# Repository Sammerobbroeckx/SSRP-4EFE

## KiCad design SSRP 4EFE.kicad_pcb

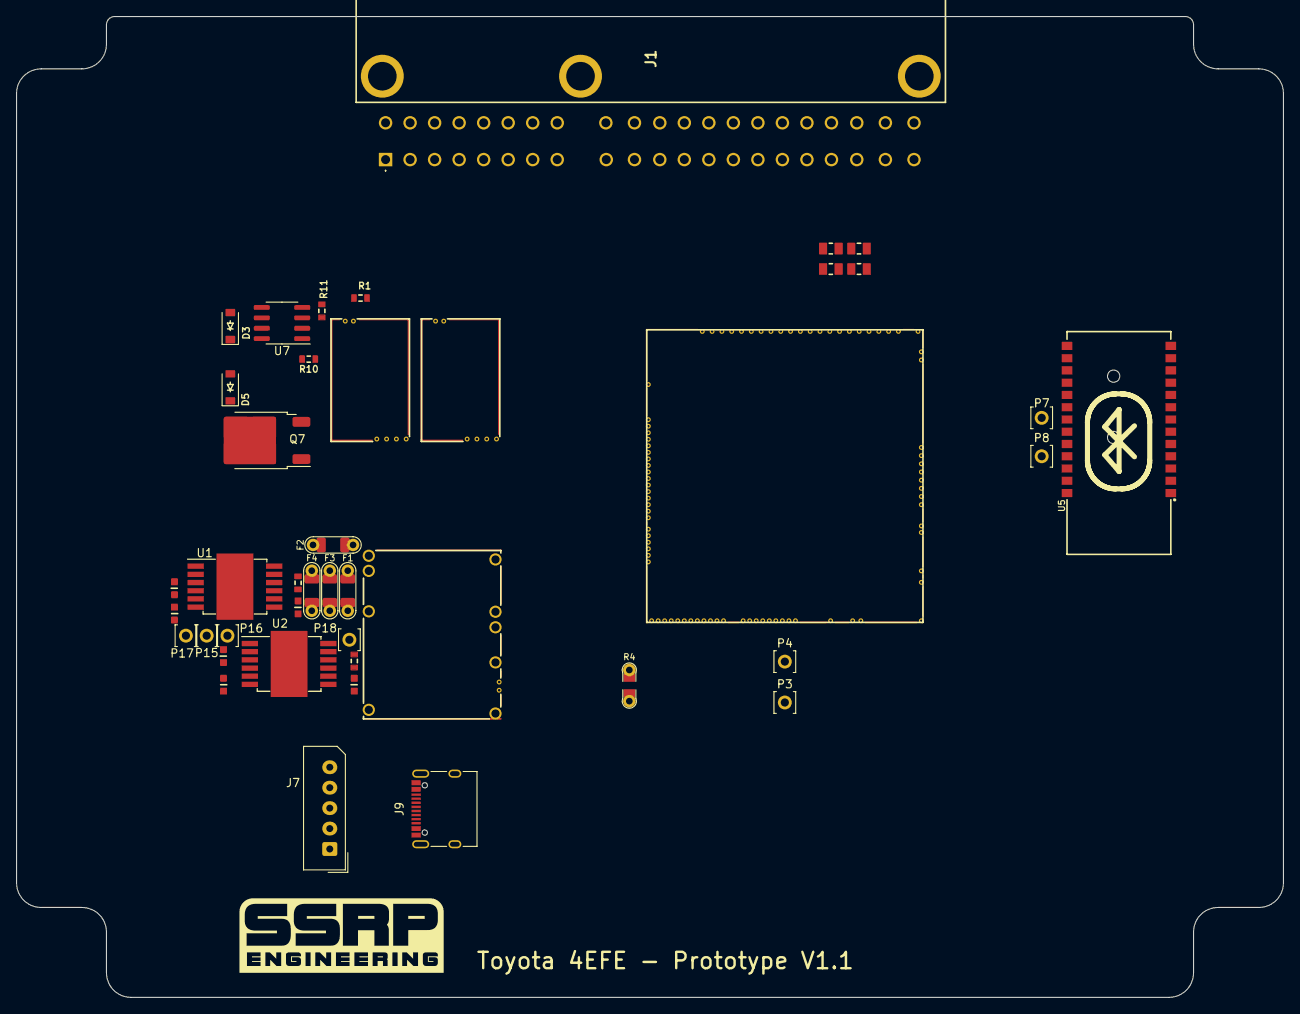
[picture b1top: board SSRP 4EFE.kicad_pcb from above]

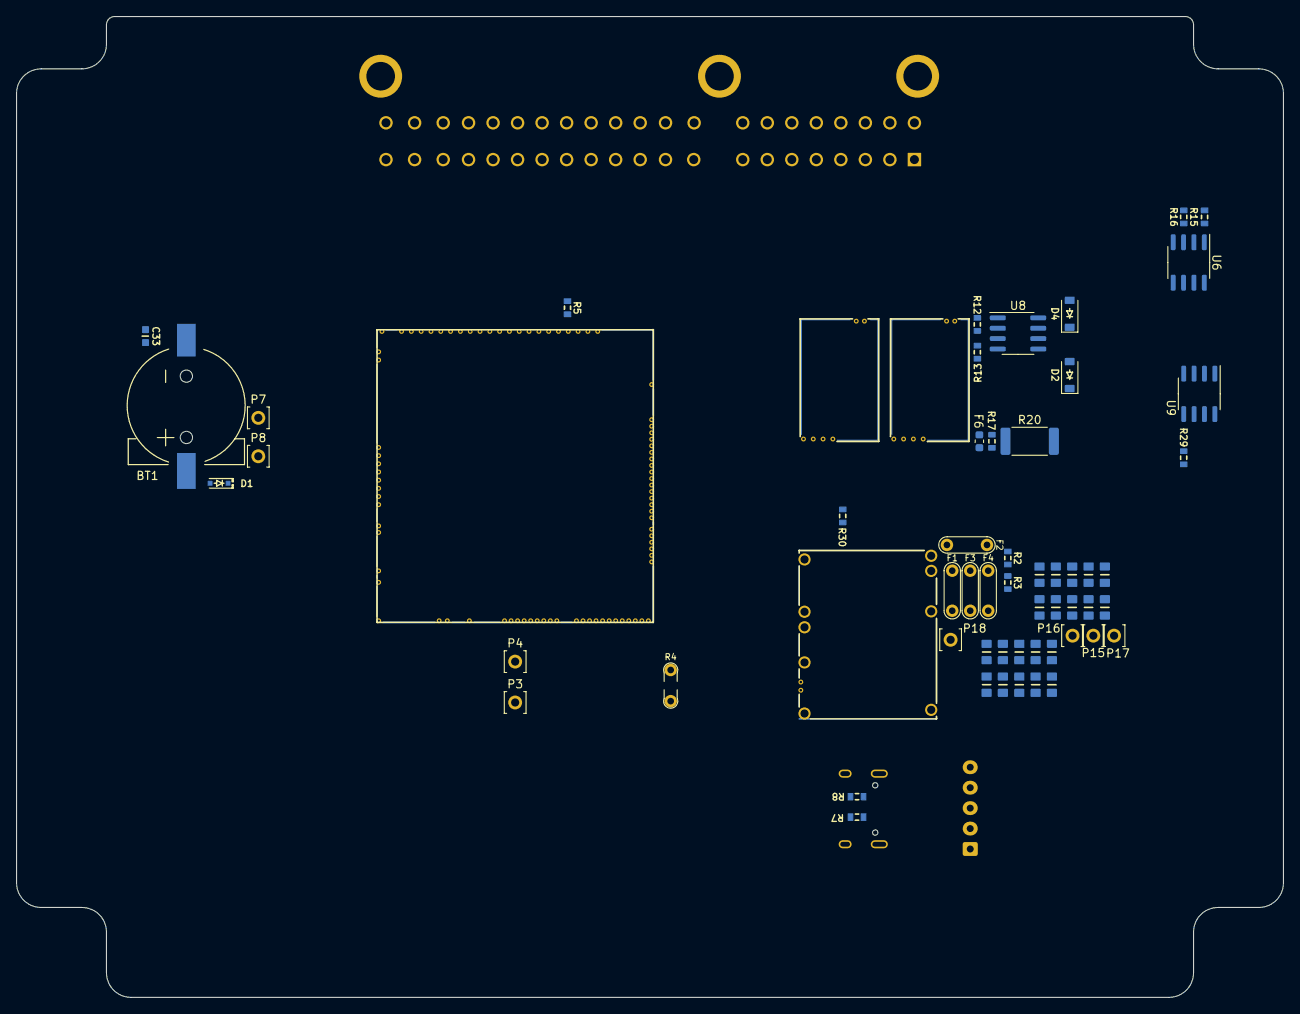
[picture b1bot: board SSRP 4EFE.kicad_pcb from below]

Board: 4 copper layers, 155.0 x 120.0 mm, 84 parts (42 on the bottom side), 61 nets, no tracks yet.

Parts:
BT1: CR1220; CR1220-2
C1, C2, C3, C4, C5, C6, C7, C8, C9, C10, C14, C15, C16, C17, C18, C19, C20, C21, C22, C23: 10u; C0805
C11, C24, C33: 100n; C0603
C12, C13, C25, C26: 10n; C0603
D1: 1N4148WS; SOD-323
D2, D3, D4, D5: B5819W; SOD-123
F1, F2, F3, F4: 12H1500D; PAD-1206-PAD
F6: 50mA; Fuse_0603_1608Metric
J1: 175446-6; 1754466
J7: Conn_01x05_Male; Molex_SPOX_5267-05A_1x05_P2.50mm_Vertical
J9: USB_C
M1: Module-power_12and5V-0.2; power_12and5V
M3: Module-vr-discrete-0.5; vr-discrete
M4: Module-vr-max9924-0.1; vr-max9924
M6: Module:mega-mcu100/0.3; mega-mcu100
P3, P4, P7, P8, P15, P16, P17, P18: Pad; PAD-TH
Q7: ISL9V3040D3ST; TO-252-2
R1, R9, R10, R11, R12, R13, R14, R15, R16, R29, R30: 4.7k; R0603
R2: 33k; R0603
R3: 6.8k; R0603
R4: Jumper-Pad-Pad; PAD-0805-PAD
R5: 0; R0603
R7, R8: 5.6k; R0603
R17: 22; R0603
R20: 0; R_2512_6332Metric
R35, R36: 10k; R0805
R38, R39: DNP; R0805
U1, U2: TLE9201SG; Infineon_PG-DSO-12-11
U5: JDY-33
U6, U7, U8, U9: VNLD5160TR-E; SOIC-8_3.9x4.9mm_P1.27mm

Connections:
+3.3V: M6.N21 (V33), R9.2, R14.2, U1.2 (VSO), U2.2 (VSO)
+3.3VA: C33.2, M6.N15 (V33_SWITCHABLE), U5.12 (3V3)
+5V: M1.E4 (V5), M6.N22 (VCC)
+5VA: M3.E4 (V5_IN), M4.E4 (V5_IN), M6.E1 (V5A_SWITCHABLE), M6.W2 (V5A_SWITCHABLE), R38.2, R39.2
+5VP: M1.V4 (5VP), R1.1
+12V: F2.1, F3.1, F4.1, R2.2
+12V_RAW: D2.1 (K), D3.1 (K), D4.1 (K), D5.1 (K), F2.2, M1.V1 (V12_PERM), M1.V3 (V12_RAW)
/ADC3: M6.S15 (IN_KNOCK_(PA2)), R5.2
/DC1_DIR: M6.E21 (OUT_PWM4_(PC8)), P15.1, U1.1 (DIR)
/DC1_DIS: R9.1, U1.11 (DIS)
/DC1_PWM: M6.E20 (OUT_PWM3_(PC7)), P17.1, U1.12 (PWM)
/DC2_DIR: P16.1, U2.1 (DIR)
/DC2_DIS: M6.N4 (USBID_(PA10)), R14.1, U2.11 (DIS)
/DC2_PWM: M6.E22 (OUT_PWM5_(PC9)), P18.1, U2.12 (PWM)
/DC Driver 1/PWR: C1.2, C2.2, C3.2, C4.2, C5.2, C6.2, C7.2, C8.2, C9.2, C10.2, C11.2, F4.2, U1.4 (VS)
/DC Driver 2/PWR: C14.2, C15.2, C16.2, C17.2, C18.2, C19.2, C20.2, C21.2, C22.2, C23.2, C24.2, F3.2, U2.4 (VS)
/IGN1: F6.2, M6.W10 (IGN1_(PC13))
/INJ1: M6.E17 (OUT_INJ1_(PD3)), R29.2, U9.1 (IN1)
/INJ2: M6.E16 (OUT_INJ2_(PA9)), R30.2, U9.3 (IN2)
/IN_BUTTON1: M6.S14 (IN_CRANK_(PB1)), R35.2, R38.1
/IN_BUTTON2: M6.S16 (IN_CAM_(PA6)), R36.2, R39.1
/IN_VIGN: F1.2, M1.V2 (IN_VIGN)
/IN_VMAIN: M6.S6 (IN_AUX4_(PC5)), R2.1, R3.2
/LS1: M6.E11 (OUT_INJ7_(PD15)), R10.2, U7.1 (IN1)
/LS2: M6.E10 (OUT_INJ8_(PD12)), R11.2, U7.3 (IN2)
/LS3: M6.E18 (OUT_PWM1_(PD13)), R12.2, U8.1 (IN1)
/LS4: M6.E19 (OUT_PWM2_(PC6)), R13.2, U8.3 (IN2)
/LS_HOT1: M6.W4 (IGN7_(PB9)), R16.1, U6.3 (IN2)
/LS_HOT2: M6.W3 (IGN8_(PE6)), R15.1, U6.1 (IN1)
/OUT_DC1+: C13.2, U1.7 (OUT2)
/OUT_DC1-: C12.2, U1.5 (OUT1)
/OUT_DC2+: C26.2, U2.7 (OUT2)
/OUT_DC2-: C25.2, U2.5 (OUT1)
/OUT_IGN1: Q7.2 (C), R20.2
/OUT_LS1: D2.2 (A), U7.8 (D1)
/OUT_LS2: D3.2 (A), U7.6 (D2)
/OUT_LS3: D4.2 (A), U8.8 (D1)
/OUT_LS4: D5.2 (A), U8.6 (D2)
/PWR_EN: M1.E5 (EN_5VP), M6.N20 (OUT_PWR_EN_(PE10))
/USB+: J7.3, J9.A6 (D+), J9.B6 (D+), M6.N3 (USBP_(PA12))
/USB-: J7.2, J9.A7 (D-), J9.B7 (D-), M6.N2 (USBM_(PA11))
/VBAT: D1.1 (K), M1.E1 (VBAT), M6.N17 (VBAT)
/VBUS: J7.1, J9.A4 (VBUS), J9.A9 (VBUS), J9.B4 (VBUS), J9.B9 (VBUS), M6.N1 (VBUS)
/VIGN: M1.E3 (VIGN), M6.E5 (IN_VIGN_(PA5))
/VR_DISCRETE: M3.E3 (OUT), M6.N18 (UART8_RX_(PE0))
/VR_DISCRETE_A: M3.E2 (OUT_A), R5.1
/VR_DISCRETE_THR: M3.E1 (Thresh_IN), M6.E23 (OUT_PWM6_(PD14))
/VR_MAX9924: M4.E3 (OUT), M6.N19 (UART8_TX_(PE1))
/VR_MAX9924-: M4.W1 (VR-), R1.2
GND: BT1.2 (-), C1.1, C2.1, C3.1, C4.1, C5.1, C6.1, C7.1, C8.1, C9.1, C10.1, C11.1, C12.1, C13.1, C14.1, C15.1, C16.1, C17.1, C18.1, C19.1, C20.1, C21.1, C22.1, C23.1, C24.1, C25.1, C26.1, C33.1, J7.4, J7.5, J9.A1 (GND), J9.A12 (GND), J9.B1 (GND), J9.B12 (GND), J9.S1 (SHIELD), M1.S1 (GND), M3.G (GND), M4.G (GND), M6.G (GND), Q7.3 (E), R3.1, R7.1, R8.1, R10.1, R11.1, R12.1, R13.1, R15.2, R16.2, R29.1, R30.1, U1.6 (GND), U1.8 (SI), U1.9 (CSN), U1.10 (SCK), U1.13 (GND), U2.6 (GND), U2.8 (SI), U2.9 (CSN), U2.10 (SCK), U2.13 (GND), U5.13 (GND), U6.5 (S2), U6.7 (S1), U7.5 (S2), U7.7 (S1), U8.5 (S2), U8.7 (S1), U9.5 (S2), U9.7 (S1)
GNDA: M6.W1 (GNDA), R35.1, R36.1
unnamed: BT1.1 (+), D1.2 (A)
unnamed: F6.1, R17.2, R20.1
unnamed: J9.A5 (CC1), R7.2
unnamed: J9.B5 (CC2), R8.2
unnamed: M1.E6 (PG_5VP), R4.1
unnamed: M6.N14a (LED_GREEN), P4.1
unnamed: M6.N14b (LED_YELLOW), P3.1
unnamed: M6.N14 (UART2_RX_(PD6)), P7.1, U5.1 (TXD)
unnamed: M6.N13 (UART2_TX_(PD5)), P8.1, U5.2 (RXD)
unnamed: Q7.1 (G), R17.1

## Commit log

2024-07-07 first changes from UAEFI to 4EFE ECU PCB dimensions
